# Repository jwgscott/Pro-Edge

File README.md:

# Pro-Edge
Hardware and software for automatic edge/orgasm detection on Arduino. Built upon night-howler/protogasm.

Protogasm hasn't been updated for a few years now, yet it remains a solid base to build upon with easy-to-use hardware and software.

Pro-Edge for Arduino is pretty much feature-complete - the hardware limits are reached quite easily. Please report any bugs or errors you encounter via GitHubs "Issues" feature (including info on how to reproduce, when encountered etc.). Also, please use the "Issues" feature to share ideas for changes or features. I'll try to work on them when I have time.

## Features
Pro-Edge takes all the features from Protogasm and extends them (while fixing a few bugs...).

* The previously announced (but never added) Protogasm feature of configurable vibrator ramp-up speed has been implemented.
* The Automatic Edging mode has been majorly reworked. It now features configurable smooth or abrupt drop mode and a denial or release mode.
* Release mode allows the user to have a (pre-defined) orgasm after a set number of edges are reached. It features a progress bar.
* When in release mode, the device runs an anti-cheat logic, preventing the user from accumulating edges without really putting in the work. (Not completely impossible to circumvent but pretty effective).
* There is a Variance setting to add some randomness to the set target edges, requiring more or less than the set amount while lying to the user with the progress bar.

### The Automatic Edging mode
Building upon the automatic edging mode from Protogasm, this mode now features a lot of possible customization.

#### Abrupt edging mode
Abrupt edging mode increases vibrator strength to a set maximum and keeps it there until the user reaches the set limit. It then cuts off the vibration abruptly for a defined break before starting to ramp up again. This is the basic mode featured in the original Protogasm.

#### Smooth edging mode
Smooth edging mode works slightly differently from Abrupt edging mode: it reduces the vibrator speed dynamically, depending on user arousal/clenching strength. After the arousal reading decreases for a moment, the vibration gets more intense again. Rinse and repeat.
When the user clenches quite hard (hitting the set edge detection, depending on the configured sensitivity), the device switches off the vibrator completely—just as in Abrupt edging mode—before starting the configured ramp-up again after some time.
It's quite devious and much better at keeping the user close to the edge for extended periods by giving just enough stimulation to feel tantalizingly intense. It is also easier to calibrate for extremely close edges with a near impossibility of orgasm.

#### Denial mode
In Denial mode, the cycle just continues without end, edging the user over and over without ever granting release, either using abrupt or smooth edging mode.

#### Release mode
In Release mode, the user is edged over and over, just like in Denial mode, but accumulates reached edges. After a predefined number of edges are reached, the vibrator stays on (for a predefined time) after registering an edge, granting the user a release. Progress is visualized via an indicator using the built-in LEDs.
There is a Variance setting to add some randomness to the set target edges, requiring more or less than the set amount while possibly lying to the user with the progress bar as it only shows the user defined target edges without the random variance.
Furthermore, this release can come with a twist: the release duration (the time the vibrator operates at the user-configured maximum setting) is also configurable. This allows for a ruined orgasm with a very short release duration, a full orgasm, or prolonged overstimulation (POT) with a longer duration.
When in release mode, the device runs an anti-cheat logic, preventing the user from accumulating edges without really putting in the work. (Not completely impossible to circumvent but pretty effective).

### Bugfixes (some)
* Fixed timer clock speed issue: The issue where the vibrator only operated at full speed when set to the maximum speed setting has been fixed.
* Fixed standby behavior: Resolved an issue where the device failed to properly enter standby mode or restarted upon a very long button press.
* Some more unmentioned ones by now. See changelog in /documents for details.

## Hardware
The hardware remains largely unchanged, with this repo providing a ready-to-print, easy-to-solder PCB designed to be easily mounted on an Arduino UNO R3 like a normal plug-and-play Arduino shield.

I still need to compile an updated BOM for the shield but it is almost completely in line with the original Protogasm hardware, so...

The new Pro-Edge software should™ be install and go on any Arduino UNO R3 based Protogasm hardware. At least that's the hardware I tested it with. It probably works with the R4 etc. as well, though untested and without guarantees.

I have created a modified case for the Protogasm a few years ago - it works for me at the moment but requires some changes before I feel good about publishing it here. Maybe that'll happen in the future.

## License
This work is licensed under a Creative Commons Attribution-NonCommercial 4.0 International Licence, available at http://creativecommons.org/licenses/by-nc/4.0/.

## Disclaimer
The hardware designs, schematics, source code, and documentation in this repository are provided "AS IS", without warranty of any kind, express or implied. This includes, but is not limited to, the implied warranties of merchantability, fitness for a particular purpose, and non-infringement. This project involves DIY electronics, mechanical assembly, and software integration for a device intended for personal use. Building and operating uncertified DIY hardware carries inherent dangers, including but not limited to electrical shock, burns, physical injury, and risks related to material toxicity or poor hygiene. The device has not been tested, evaluated, or approved by any regulatory health or safety agency (e.g., FDA, CE, EMA). By choosing to build, modify, or use this project, you voluntarily assume all physical and legal risks associated with its assembly and operation.

This project is strictly an experimental adult novelty item intended for educational and DIY purposes. It is absolutely not a medical device and should not be used as such. This repository and its resulting hardware are intended solely for use by consenting adults (18 years of age or older, or the age of majority in your jurisdiction).

The provided software is experimental. The author does not guarantee that the code is free from bugs, vulnerabilities, or exploits. If this device (in the future) utilizes wireless connectivity (e.g., Bluetooth, Wi-Fi, or internet networking), you acknowledge the inherent privacy and security risks associated with connecting intimate hardware to a network. The user is solely responsible for securing their own data, networks, and operational environments.

IN NO EVENT SHALL THE AUTHORS, CREATORS, CONTRIBUTORS, OR COPYRIGHT HOLDERS BE LIABLE FOR ANY CLAIM, DAMAGES (INCLUDING BUT NOT LIMITED TO DIRECT, INDIRECT, INCIDENTAL, SPECIAL, EXEMPLARY, OR CONSEQUENTIAL DAMAGES), PERSONAL INJURY, OR OTHER LIABILITY, WHETHER IN AN ACTION OF CONTRACT, TORT, OR OTHERWISE, ARISING FROM, OUT OF, OR IN CONNECTION WITH THE REPOSITORY, THE HARDWARE, THE SOFTWARE, OR THE USE OR OTHER DEALINGS IN THE PROJECT.

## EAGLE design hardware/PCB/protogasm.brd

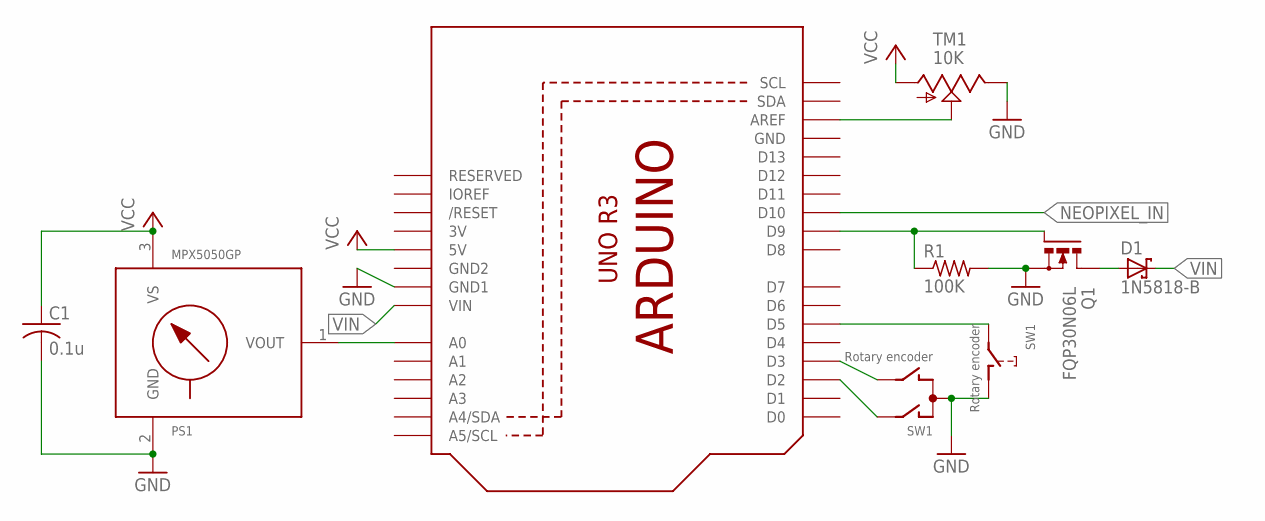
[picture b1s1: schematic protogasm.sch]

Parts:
C1: 0.1u; C025-025X050
D1: 1N5818-B; DO41-7.6
PS1: MPX5050GP; 867B-H
Q1: FQP30N06L; TO220BH
R1: 100K; 0207/10
SW1: Rotary encoder; ALPS_EC12E_SW
TM1: 10K; 6MM
U1: ARDUINOR3PERF; PERF

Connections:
3V: U1.3V, U1.3V. (3V)
GND: C1.2, PS1.2 (GND), Q1.S, R1.2, SW1.C, SW1.D (1), TM1.E, U1.GND, U1.GND1, U1.GND1. (GND1), U1.GND. (GND)
GND2: U1.GND2, U1.GND2. (GND2)
unnamed: SW1.A, U1.D2, U1.D2. (D2)
unnamed: SW1.B, U1.D3, U1.D3. (D3)
unnamed: SW1.E (2), U1.D5, U1.D5. (D5)
unnamed: TM1.S, U1.AREF, U1.AREF. (AREF)
unnamed: Q1.G, R1.1, U1.D9, U1.D9. (D9)
unnamed: D1.A, Q1.D
unnamed: PS1.1 (VOUT), U1.A0, U1.A0. (A0)
NEOPIXEL_IN: U1.D10, U1.D10. (D10)
VCC: C1.1, PS1.3 (VS), TM1.A, U1.5V, U1.5V. (5V)
VIN: D1.C, U1.VIN, U1.VIN. (VIN)

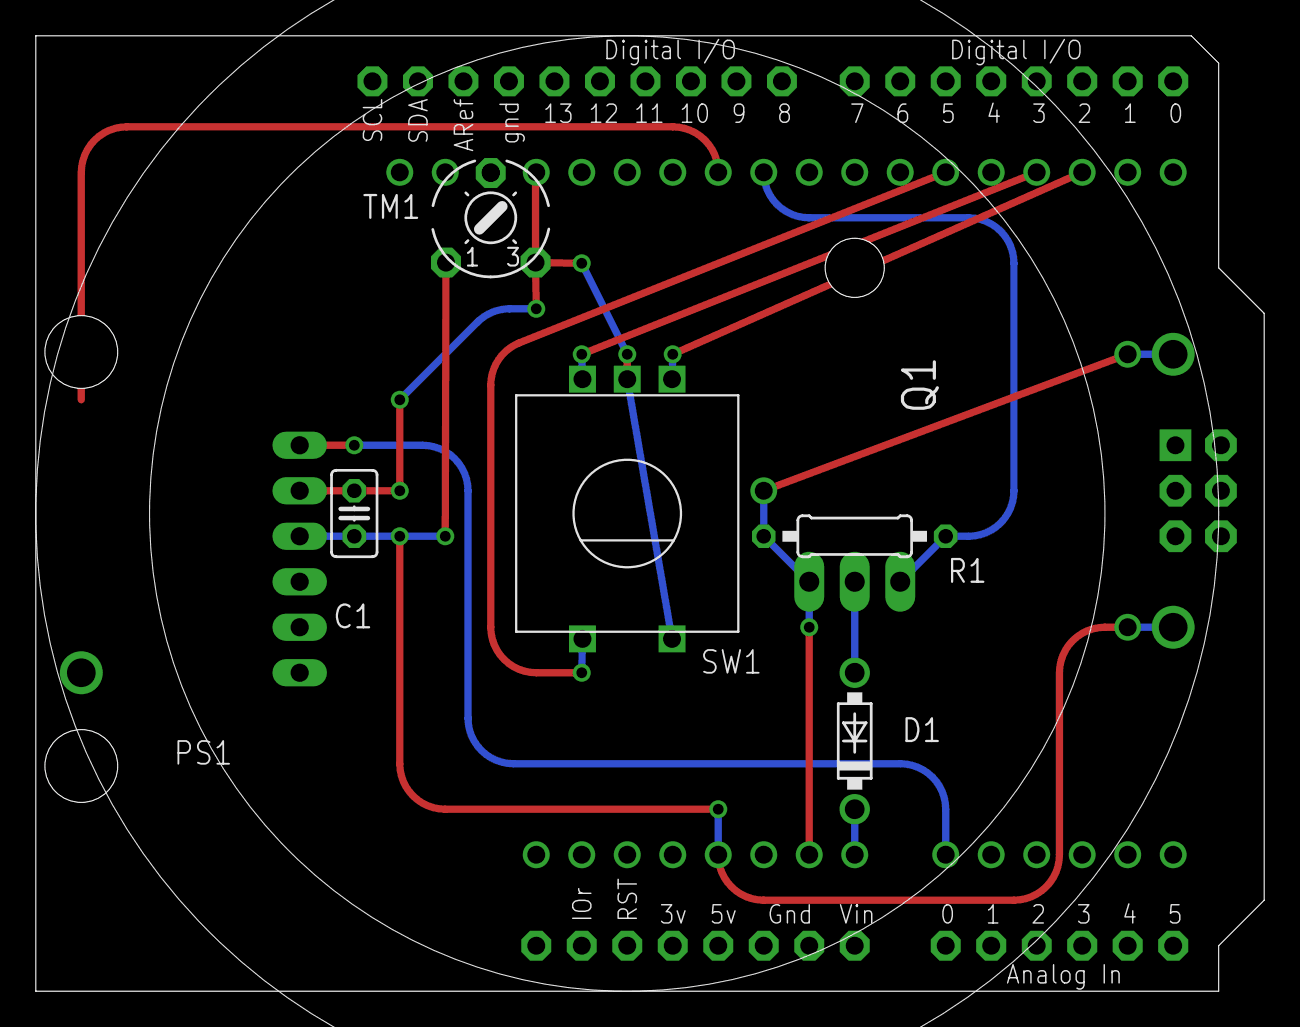
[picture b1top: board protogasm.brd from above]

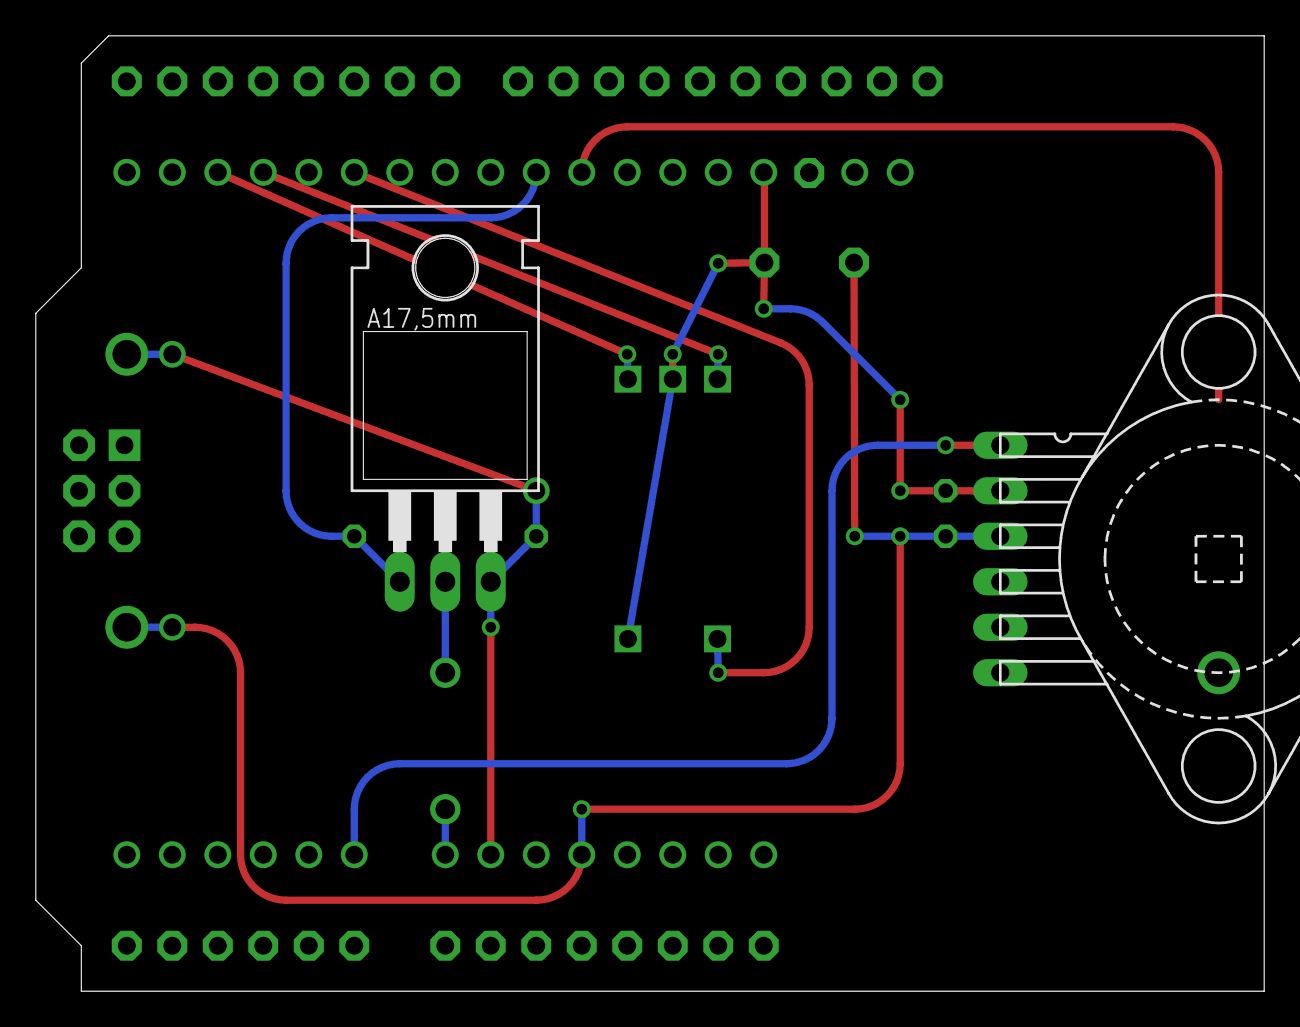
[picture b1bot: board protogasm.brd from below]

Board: 2 copper layers, 68.6 x 53.3 mm, 8 parts (2 on the bottom side), 13 nets.

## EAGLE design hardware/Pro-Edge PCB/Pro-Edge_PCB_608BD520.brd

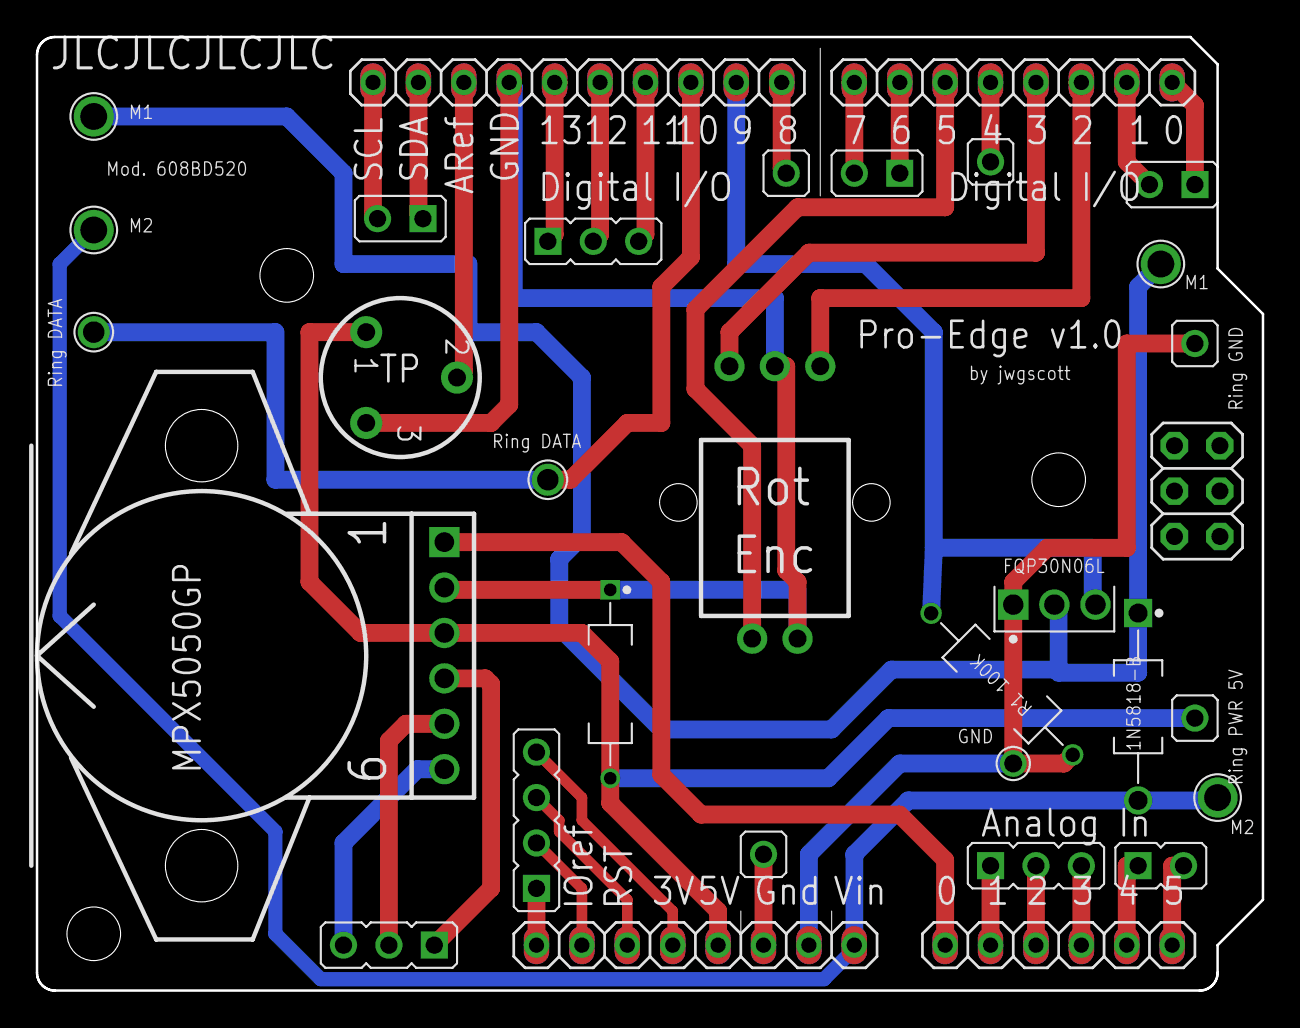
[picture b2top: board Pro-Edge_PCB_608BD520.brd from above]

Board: 2 copper layers, 68.6 x 53.3 mm, 32 parts (0 on the bottom side), 36 nets.

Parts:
AD: 6x1F-H8.5; 1X06
C1: CAPPAD1054W51L660D241
D1: 1N5818G; DIOAD1048W78L520D270_AD2
ICSP: 3x2 M; 2X03
IOH: 10x1F-H8.5; 1X10
IOL: 8x1F-H8.5; 1X08
J1, J2, J7, J8, J9: JMP1
J3, J4, J6: JMP1Q
J5, J11, J13: JMP3
J10: JMP4
J12: JMP2
POWER: 8x1F-H8.5; 1X08
Q1: 1W, 23W; TO230P670X250X920-3
R1: CFR50SJT-52-11K; RESAD1120W55L680D260_AD1
U1: NXP_SEMICONDUCTOR-SOT1852-1-03_2016-J-MFG; NXP_Semiconductor-SOT1852-1-03_2016-J-MFG
U2: ROTARYENCODER1; RotaryEncoder1
U3: TRIMPOTI10K; TrimPoti10K
WIRE1: AWG20
WIRE2, WIRE3: AWG18
WIRE4, WIRE5, WIRE6, WIRE7: AWG16

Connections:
Net_0: C1.2, J1.1, POWER.5, U1.4, U3.1
Net_1: C1.1, IOH.7, U1.5, U2.2, U2.5, U3.3
Net_2: AD.1, U1.1
Net_3: IOL.3, U2.3
Net_4: IOL.4, U2.1
Net_5: IOL.6, U2.4
Net_6: D1.2, POWER.8, WIRE4.WIRE, WIRE7.WIRE
Net_7: D1.1, Q1.2, WIRE5.WIRE, WIRE6.WIRE
Net_8: IOH.2, Q1.3, R1.1
Net_9: J2.1, POWER.7, Q1.1, R1.2, WIRE1.WIRE
Net_10: IOH.8, U3.2
Net_11: IOH.3, WIRE2.WIRE, WIRE3.WIRE
Net_12: IOL.1, J4.1
Net_13: IOL.2, J4.2
Net_14: IOL.7, J3.1
Net_15: IOL.8, J3.2
Net_16: IOH.4, J5.3
Net_17: IOH.5, J5.2
Net_18: IOH.6, J5.1
Net_19: IOH.9, J6.1
Net_20: IOH.10, J6.2
Net_21: IOH.1, J7.1
Net_22: IOL.5, J8.1
Net_23: J10.1, POWER.1
Net_24: J10.2, POWER.2
Net_25: J10.3, POWER.3
Net_26: J10.4, POWER.4
Net_27: AD.2, J11.1
Net_28: AD.3, J11.2
Net_29: AD.4, J11.3
Net_30: AD.5, J12.1
Net_31: AD.6, J12.2
Net_32: J13.1, U1.3
Net_33: J13.2, U1.2
Net_34: J13.3, U1.6
Net_35: J9.1, POWER.6
